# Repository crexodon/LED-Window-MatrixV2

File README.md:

# LED-Window-Matrix Neo

Complete new version of our last semester's [project](https://github.com/Boslx/LED-Window-Matrix). 

## New Features
- Complete rewrite of the mesh using ESP-MDF
- UDP based bridge for easy and fast communication
- Updated [PixelBridge](https://github.com/crexodon/PixelBridge)
- (Planned) Management Software for End User

## Old Media
https://user-images.githubusercontent.com/36489816/166237971-5a803816-1b47-4246-80e3-ec737a2a25ef.mp4

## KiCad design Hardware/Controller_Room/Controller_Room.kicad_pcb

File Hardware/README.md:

# Hardware
This folder contains our hardware designs for the matrix.

## Controller_Room
The room controller is a ESP32 PCB that features:  
- RS485 Transciever for the LEDs
- Power Switch and Sense
- Environment Sensors
- (Optional) LAN Interface
- (Optional) SD Card slot

## Controller_Window
The window controller is a WS2811 PCB that features:
- 2x RS485 Transciever for Data In and Out
- MosFETs to drive ~6m of RGB LED Strip

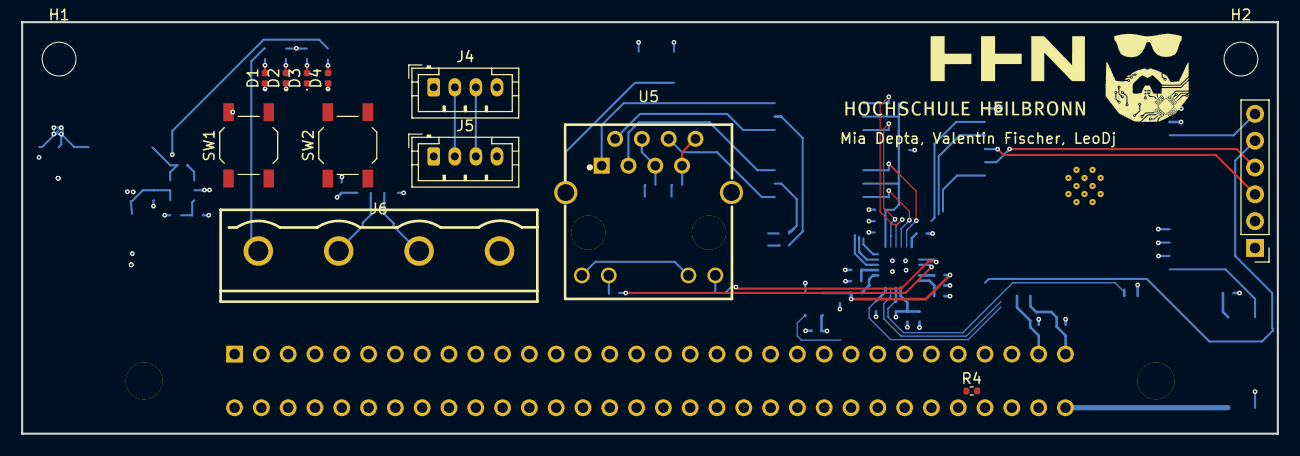
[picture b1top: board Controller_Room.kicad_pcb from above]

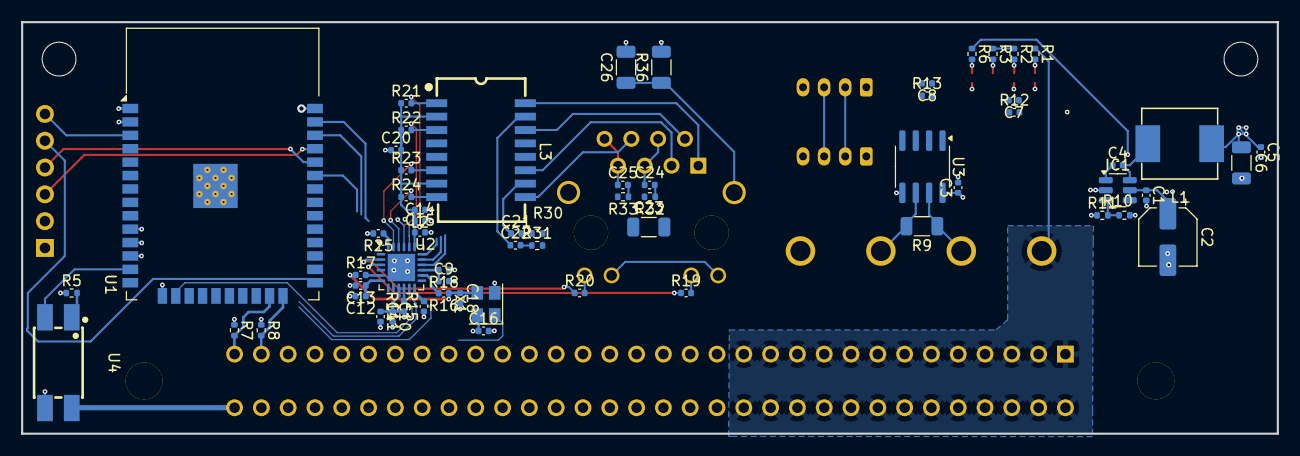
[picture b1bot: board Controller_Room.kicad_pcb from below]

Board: 4 copper layers, 119.0 x 39.0 mm, 79 parts (63 on the bottom side), 67 nets.

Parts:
C1, C3, C4, C5, C7, C8, C9, C11, C13, C15, C16, C20, C21, C22, C24, C25: 100n; C_0402_1005Metric
C2: 47u; CP_Elec_5x5.4
C6: 10u; C_1206_3216Metric
C10, C12, C14: 10u; C_0402_1005Metric
C18: NC; C_0402_1005Metric
C23, C26: 1000pF/2KV; C_1206_3216Metric
D1, D2, D3, D4: LED; LED_0402_1005Metric
H1, H2, H3, H4: MountingHole; MountingHole_3.2mm_M3
IC1: RY8310; SOT-23-6
J3: HP DPS; CONN-TH_64P-P2.54_ED64MEBGFBK
J4, J5: Conn_01x04_Female; JST_PH_B4B-PH-K_1x04_P2.00mm_Vertical
J6: Conn_01x04_Female; CONN-TH_4P-P7.62_DB2EVC-7.62-4P
J7: Conn_01x06_Female; PinHeader_1x06_P2.54mm_Vertical
L1: 4.7u; L_0630
L2: L_Ferrite; C_0402_1005Metric
L3: B1608S
R1, R6, R11: 10k; R_0402_1005Metric
R2, R3: 1k; R_0402_1005Metric
R4: 22k; R_0402_1005Metric
R5: R; R_0402_1005Metric
R7, R8: 4k7; R_0402_1005Metric
R9: Nc; R_1206_3216Metric
R10: 31,25k; R_0402_1005Metric
R12, R13: 4k7; C_0402_1005Metric
R14, R18: 10k; C_0402_1005Metric
R15: 1.5k; C_0402_1005Metric
R16, R17: 33; C_0402_1005Metric
R19, R20: 1k; C_0402_1005Metric
R21, R22, R23, R24: 49R9; C_0402_1005Metric
R25: 12k1; C_0402_1005Metric
R30, R31, R32, R33: 75; R_0402_1005Metric
R36: 0; C_1206_3216Metric
SW1: Reset; SW_SPST_TL3342
SW2: User; SW_SPST_TL3342
U1: ESP32-WROOM-32
U2: LAN8720A; QFN-24-1EP_4x4mm_P0.5mm_EP2.6x2.6mm
U3: MAX3485; SOIC-8_3.9x4.9mm_P1.27mm
U4: EL817S1(C)(TU)-F; OPTO-SMD-4_L4.6-W6.5-P2.54-LS10.3-TL
U5: RC01931; RJ45-TH_RCH_RC01931
X1: ASV-50MHz; Oscillator_SMD_Abracon_ASE-4Pin_3.2x2.5mm

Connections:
+3.3VA: C14.1, C15.1, C20.2, L2.2, L3.2 (TCT), L3.7 (RCT), R21.1, R22.1, R23.1, R24.1, U2.1 (VDD2A), U2.19 (VDD1A), U5.9 (LED+), U5.11 (LED+)
+3V3: C3.1, C5.1, C6.1, C10.1, C11.1, C16.1, J4.1, J5.1, J7.1, L1.2, L2.1, R2.1, R3.1, R5.1, R7.1, R8.1, R10.2, R12.1, R13.1, R14.1, R15.1, R18.1, U1.2 (VDD), U2.9 (VDDIO), U3.8 (VCC), X1.4 (Vdd)
+12V: C1.1, C2.1, IC1.4 (EN), IC1.5 (IN), J3.56, R4.1, R6.1
+VSW: J3.1, J3.2, J3.3, J3.4, J3.5, J3.6, J3.7, J3.8, J3.9, J3.10, J3.11, J3.12, J3.13, J3.14, J3.15, J3.16, J3.17, J3.18, J3.19, J3.20, J3.21, J3.22, J3.23, J3.24, J3.25, J3.26, J6.1, R1.1
/HP DPS High/PRESENT#: J3.58, R4.2
/HP DPS High/PSON#: J3.64, U4.4 (COL)
A: J6.3, R9.2, U3.6 (A)
B: J6.2, R9.1, U3.7 (B)
CLK50M: C18.1, R16.1, R17.1, X1.3 (OUT)
EN: C7.1, J7.6, R12.2, SW1.2, U1.3 (EN)
ETHLEDGreen: R19.2, U5.10 (LED-)
ETHLEDYel: R20.2, U5.12 (LED-)
Earth: C23.2, C26.1, R36.1, U5.13, U5.14
GND: C1.2, C2.2, C3.2, C5.2, C6.2, C7.2, C8.2, C9.2, C10.2, C11.2, C12.2, C13.2, C14.2, C15.2, C16.2, C18.2, C20.1, C26.2, D1.1 (K), D2.1 (K), D4.1 (K), IC1.2 (GND), J3.27, J3.28, J3.29, J3.30, J3.31, J3.32, J3.33, J3.34, J3.35, J3.36, J3.37, J3.38, J3.39, J3.40, J3.41, J3.42, J3.43, J3.44, J3.45, J3.46, J3.47, J3.48, J3.49, J3.50, J3.51, J3.52, J3.59, J4.4, J5.4, J6.4, J7.2, R11.1, R25.2, R36.2, SW1.1, SW2.1, U1.1 (GND), U1.15 (GND), U1.38 (GND), U1.39 (GND), U2.25 (VSS), U3.5 (GND), U4.3 (EM), X1.2 (GND)
IO0: J7.5, R16.2, U1.25 (IO0), U2.14 (INT/REFCLKO)
IO13_RXER: R14.2, U1.16 (IO13), U2.10 (RXER/PHYAD0)
IO16_OSC_EN: U1.27 (IO16), X1.1 (EN)
IO18_MDIO: R15.2, U1.30 (IO18), U2.12 (MDIO)
IO19_TXD0: U1.31 (IO19), U2.17 (TXD0)
IO21_TXEN: U1.33 (IO21), U2.16 (TXEN)
IO22_TXD1: U1.36 (IO22), U2.18 (TXD1)
IO23_MDC: U1.37 (IO23), U2.13 (MDC)
IO25_RXD0: U1.10 (IO25), U2.8 (RXD0/MODE0)
IO26_RXD1: U1.11 (IO26), U2.7 (RXD1/MODE1)
IO27_CRS_DV: U1.12 (IO27), U2.11 (CRS_DV/MODE2)
unnamed: C21.2, R30.1
unnamed: C22.2, R31.1
unnamed: C23.1, R30.2, R31.2, R32.2, R33.2
unnamed: C24.1, U5.4, U5.5
unnamed: C24.2, R32.1
unnamed: C25.1, U5.7, U5.8
unnamed: C25.2, R33.1
unnamed: D1.2 (A), R1.2
unnamed: D2.2 (A), R2.2
unnamed: D3.2 (A), R3.2
unnamed: D4.2 (A), R6.2
unnamed: C4.1, IC1.1 (CB)
unnamed: IC1.3 (FB), R10.1, R11.2
unnamed: C4.2, IC1.6 (SW), L1.1
unnamed: L3.11 (RX+), U5.3
unnamed: L3.9 (RX-), U5.6
unnamed: C21.1, L3.10 (RXCT)
unnamed: L3.16 (TX+), U5.1
unnamed: L3.14 (TX-), U5.2
unnamed: C22.1, L3.15 (TXCT)
unnamed: R19.1, U2.3 (LED1/REGOFF)
unnamed: R20.1, U2.2 (LED2/nINTSEL)
unnamed: R25.1, U2.24 (RBIAS)
unnamed: C12.1, C13.1, U2.6 (VDDCR)
unnamed: R5.2, U4.1 (AN)
OSCIN: R17.2, U2.5 (XTAL1/CLKIN)
PowerSW: U1.13 (IO14), U4.2 (CAT)
RS485_DE: U1.8 (IO32), U3.3 (DE)
RS485_DI: U1.26 (IO4), U3.4 (DI)
RS485_RE: U1.9 (IO33), U3.2 (~RE)
RS485_RO: U1.14 (IO12), U3.1 (RO)
RX: J7.4, U1.34 (RXD0/IO3)
RXN: L3.8 (RD-), R24.2, U2.22 (RXN)
RXP: L3.6 (RD+), R23.2, U2.23 (RXP)
SCL: J3.63, J4.3, J5.3, R7.2, U1.23 (IO15)
SDA: J3.61, J4.2, J5.2, R8.2, U1.24 (IO2)
StateLED: D3.1 (K), U1.28 (IO17)
TX: J7.3, U1.35 (TXD0/IO1)
TXN: L3.3 (TD-), R22.2, U2.20 (TXN)
TXP: L3.1 (TD+), R21.2, U2.21 (TXP)
UserButton: C8.1, R13.2, SW2.2, U1.4 (SENSOR_VP)
nRST: C9.1, R18.2, U2.15 (RST)

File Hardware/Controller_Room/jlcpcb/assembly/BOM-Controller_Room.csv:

Comment,Designator,Footprint,LCSC
ACS711xLCTR-12AB,U4,SOIC-8_3.9x4.9mm_P1.27mm,C114267
"31,25k",R10,R_0402_1005Metric,C11463
1k,"R1,R19,R2,R20,R3",R_0402_1005Metric,C11702
4.7u,L1,L_0630,C128688
Conn_01x04_Female,"J4,J5",JST_PH_B4B-PH-K_1x04_P2.00mm_Vertical,C131334
100n,"C1,C11,C13,C15,C16,C17,C3,C4,C5,C7,C8,C9",C_0402_1005Metric,C1525
10u,"C10,C12,C14",C_0402_1005Metric,C15525
Q_NPN_BEC,Q1,SOT-23,C2150
100,R26,C_0402_1005Metric,C25076
49R9,"R21,R22,R23,R24",C_0402_1005Metric,C25120
100k,R4,R_0402_1005Metric,C25741
10k,"R11,R14,R18,R6",R_0402_1005Metric,C25744
1.5k,R15,C_0402_1005Metric,C25867
4k7,"R12,R13,R5,R7,R8",C_0402_1005Metric,C25900
12k1,R25,C_0402_1005Metric,C281773
22u,C6,CP_Elec_5x5.4,C3001208
33,"R16,R17",C_0402_1005Metric,C307331
Reset,"SW1,SW2",SW_SPST_TL3342,C318887
RY8310,IC1,SOT-23-6,C370876
Conn_01x04_Female,J6,"PhoenixContact_GMSTBA_2,5_4-G-7,62_1x04_P7.62mm_Horizontal",C395901
LAN8720A,U2,QFN-24-1EP_4x4mm_P0.5mm_EP2.6x2.6mm,C45223
P-CHANNEL-MOSFET,"M1,M2",VSON-8_3.3x3.3mm_P0.65mm_NexFET,C471913
ESP32-WROOM-32,U1,ESP32-WROOM-32,C473012
MAX3485,U3,SOIC-8_3.9x4.9mm_P1.27mm,C668204
Barrel_Jack_Switch,J1,BarrelJack_10A,C706901
ASV-50MHz,X1,Oscillator_SMD_Abracon_ASE-4Pin_3.2x2.5mm,C717684
LED,D1,LED_0402_1005Metric,C71911
47u,C2,CP_Elec_5x5.4,C72515
LED,D3,LED_0402_1005Metric,C74338
L_Ferrite,L2,C_0402_1005Metric,C76891
LED,D2,LED_0402_1005Metric,C88330
15V,D4,D_0402_1005Metric,
MountingHole,H1,MountingHole_3.2mm_M3,
Conn_01x06_Female,J7,PinHeader_1x06_P2.54mm_Vertical,
Conn_01x02_Female,J8,PinHeader_1x02_P2.54mm_Vertical,
MountingHole,H4,MountingHole_3.2mm_M3,
MountingHole,H3,MountingHole_3.2mm_M3,
Nc,R9,R_0402_1005Metric,
MountingHole,H2,MountingHole_3.2mm_M3,
Conn_01x04_Female,J10,PinHeader_1x04_P2.54mm_Vertical,
NC,C18,C_0402_1005Metric,
HR911105A,J2,HR911105A,

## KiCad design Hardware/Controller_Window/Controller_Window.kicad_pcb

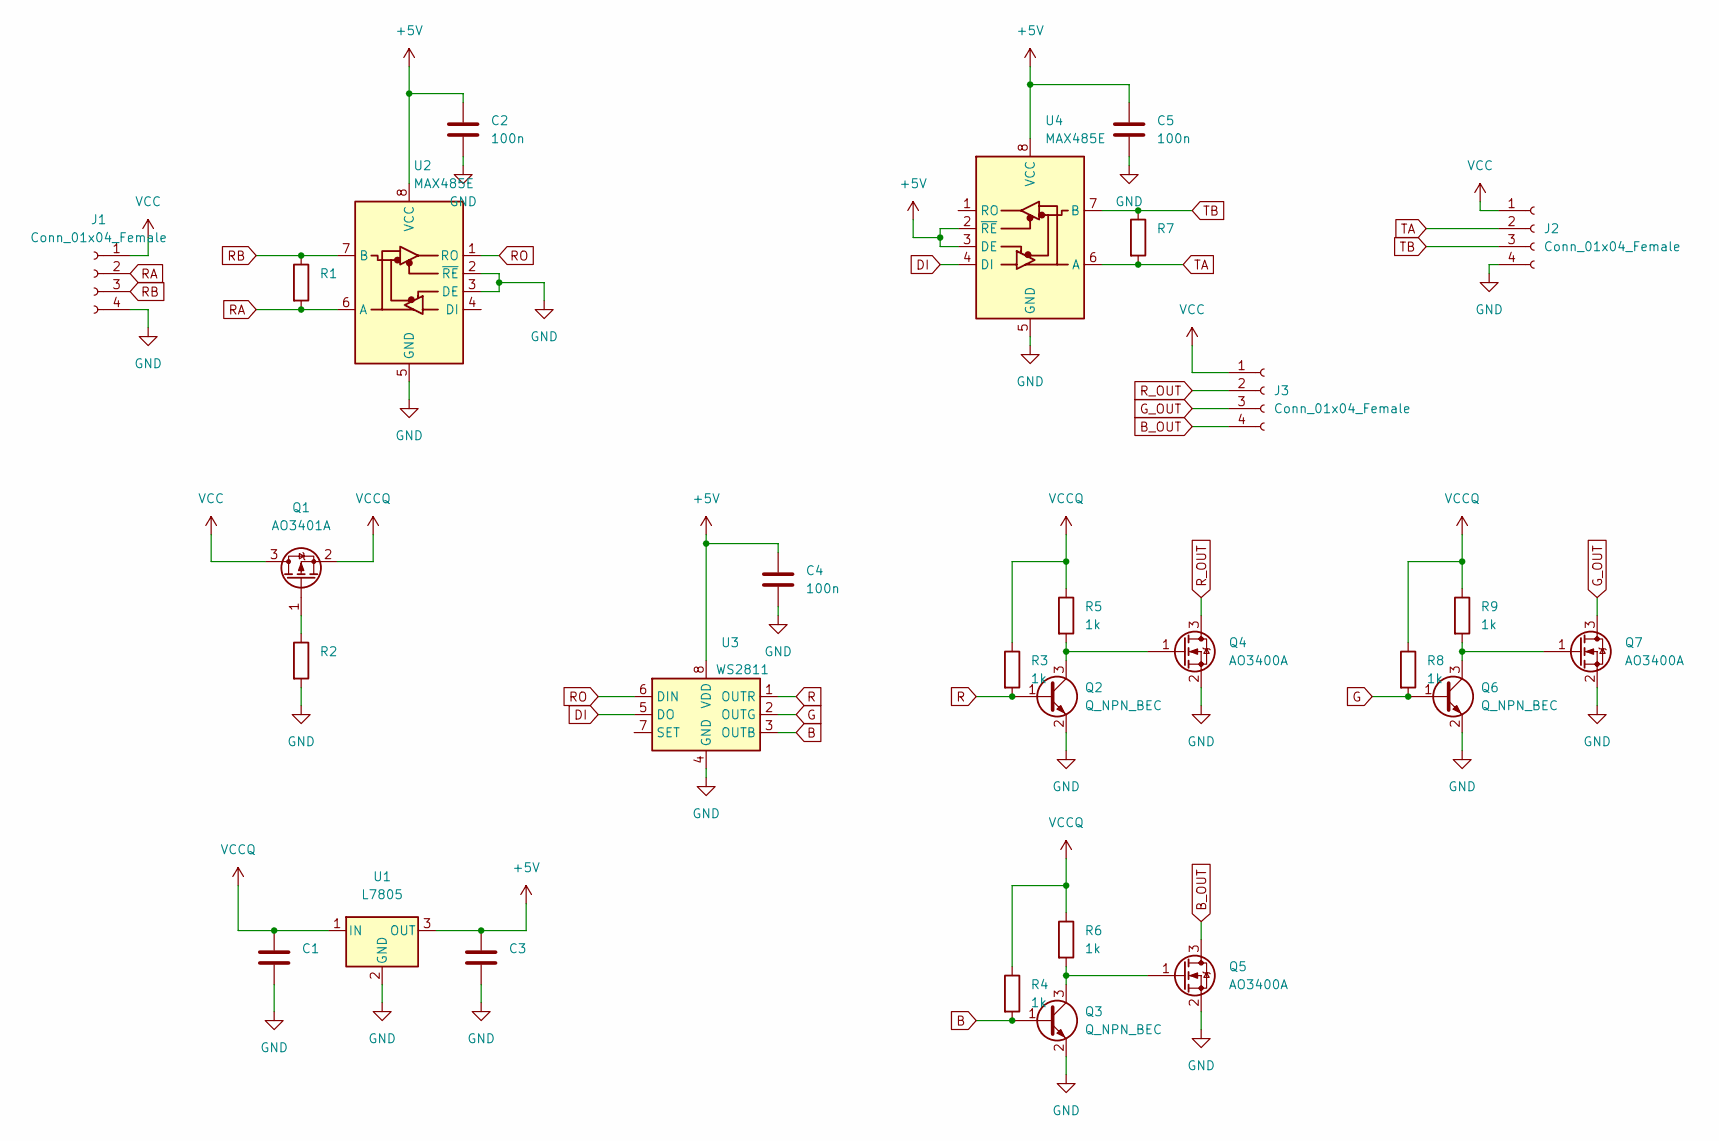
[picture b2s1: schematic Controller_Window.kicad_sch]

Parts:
C1, C3: C_0402_1005Metric
C2, C4, C5: 100n; C_0402_1005Metric
J1, J2: Conn_01x04_Female; PhoenixContact_GMSTBA_2,5_4-G-7,62_1x04_P7.62mm_Horizontal
J3: Conn_01x04_Female; JST_PH_S4B-PH-K_1x04_P2.00mm_Horizontal
Q1: AO3401A; SOT-23
Q2, Q3, Q6: Q_NPN_BEC; TSOT-23
Q4, Q5, Q7: AO3400A; SOT-23
R1, R2, R7: C_0402_1005Metric
R3, R4, R5, R6, R8, R9: 1k; C_0402_1005Metric
U1: L7805; TO-252-2
U2, U4: MAX485E; SOIC-8_3.9x4.9mm_P1.27mm
U3: WS2811; SOIC-8_3.9x4.9mm_P1.27mm

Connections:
+5V: C2.1, C3.1, C4.1, C5.1, U1.3 (OUT), U2.8 (VCC), U3.8 (VDD), U4.2 (~RE), U4.3 (DE), U4.8 (VCC)
B: Q3.1 (B), R4.2, U3.3 (OUTB)
B_OUT: J3.4, Q5.3 (D)
DI: U3.5 (DO), U4.4 (DI)
G: Q6.1 (B), R8.2, U3.2 (OUTG)
GND: C1.2, C2.2, C3.2, C4.2, C5.2, J1.4, J2.4, Q2.2 (E), Q3.2 (E), Q4.2 (S), Q5.2 (S), Q6.2 (E), Q7.2 (S), R2.2, U1.2 (GND), U2.2 (~RE), U2.3 (DE), U2.5 (GND), U3.4 (GND), U4.5 (GND)
G_OUT: J3.3, Q7.3 (D)
unnamed: Q1.1 (G), R2.1
unnamed: Q2.3 (C), Q4.1 (G), R5.2
unnamed: Q3.3 (C), Q5.1 (G), R6.2
unnamed: Q6.3 (C), Q7.1 (G), R9.2
R: Q2.1 (B), R3.2, U3.1 (OUTR)
RA: J1.2, R1.2, U2.6 (A)
RB: J1.3, R1.1, U2.7 (B)
RO: U2.1 (RO), U3.6 (DIN)
R_OUT: J3.2, Q4.3 (D)
TA: J2.2, R7.2, U4.6 (A)
TB: J2.3, R7.1, U4.7 (B)
VCC: J1.1, J2.1, J3.1, Q1.3 (D)
VCCQ: C1.1, Q1.2 (S), R3.1, R4.1, R5.1, R6.1, R8.1, R9.1, U1.1 (IN)

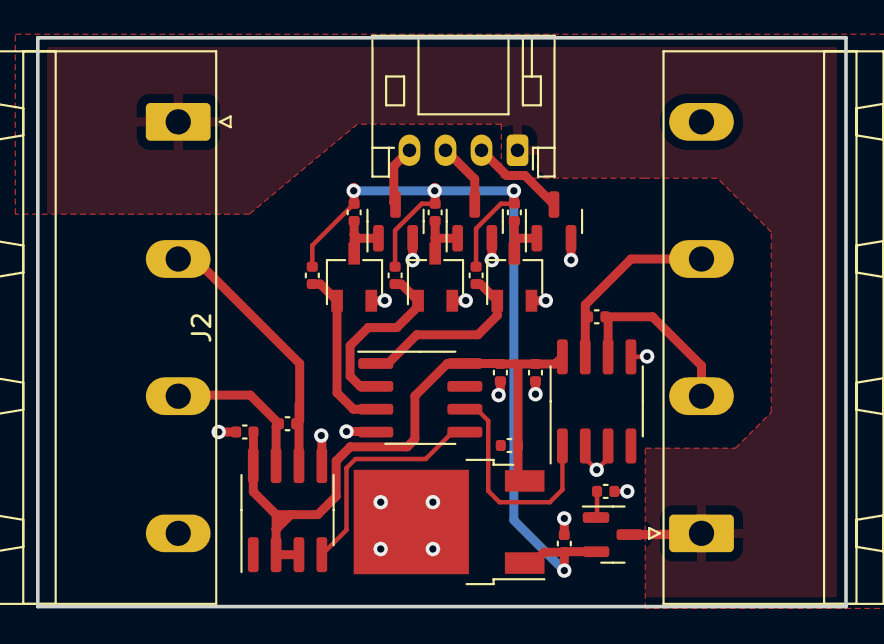
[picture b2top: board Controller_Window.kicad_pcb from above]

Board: 2 copper layers, 44.9 x 31.6 mm, 28 parts (0 on the bottom side), 20 nets.

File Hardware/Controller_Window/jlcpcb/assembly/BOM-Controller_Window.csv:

Comment,Designator,Footprint,LCSC
WS2811,U3,SOIC-8_3.9x4.9mm_P1.27mm,C114581
1k,"R1,R3,R4,R5,R6,R8,R9",C_0402_1005Metric,C11702
AO3401A,Q1,SOT-23,C15127
100n,"C1,C2,C4,C5",C_0402_1005Metric,C1525
10u,C3,C_0402_1005Metric,C15525
AO3400A,"Q4,Q5,Q7",SOT-23,C20917
Q_NPN_BEC,"Q2,Q3,Q6",TSOT-23,C2150
L7805,U1,TO-252-2,C233417
100k,R2,C_0402_1005Metric,C25741
Conn_01x04_Female,J3,JST_PH_S4B-PH-K_1x04_P2.00mm_Horizontal,C265452
MAX485E,"U2,U4",SOIC-8_3.9x4.9mm_P1.27mm,C269864
Conn_01x04_Female,"J1,J2","PhoenixContact_GMSTBA_2,5_4-G-7,62_1x04_P7.62mm_Horizontal",C395901
NC,R7,C_0402_1005Metric,

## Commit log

2022-04-28 add folders and readmes
2022-04-29 initialize two PIO ESP-MDF projects
    Template: https://github.com/maxgerhardt/pio-esp-mdf-example
2022-04-29 implement basic forwarding of data sent via UDP
2022-04-29 rename folders and add pixel bridge submodule
2022-04-29 added readme
2022-05-01 implement basic LED control over mesh
2022-05-01 implement basic OTA functionality
    currently also updates the root node by mistake with node firmware. TODO: fix
2022-05-02 fix root node getting upgraded by mistake
2022-05-02 fix reset command needing dummy byte
    remove unnecessary debug print
2022-05-02 add documentation for current UDP protocol
2022-05-02 change OTA HTTP server port
2022-05-02 remove UDP logging
2022-06-10 Added Trinity
2022-06-27 fix Submodule
2022-07-02 fixes for actual hardware
    - LED timeout and init to black so PSU doesn't get overloaded
    - correct LED pin
2022-07-18 add Hardware
2022-10-31 fix Bodges in Schematic
2022-11-02 fix bugs
2022-12-07 add submodule rest-api server
2023-01-18 add espressif version number
2023-01-18 set pin 14 high, because power measure missing
2023-01-18 add bme280 components
2023-01-18 add BMP280 component
2023-01-18 add functions for I2C and CMP280
2023-01-21 set correct pin for LED Output/Power SW
2023-01-27 add HTTP POST Request
2023-01-27 implement sensor and send sendsor data over mesh
2023-01-27 add submodule Trintiyv2
2024-10-06 Add Files
